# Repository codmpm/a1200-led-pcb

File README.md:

# A1200 LED PCB

This is a simple replacement for the original LED PCB of an Amiga 1200.

On refurbishment of my original PCB, some traces broke of as the thing is something around 30 years old ;-)
The only thing I've added, is the possibility to use 1206 33Ω resistor instead of the throughhole ones.

The Boards can be ordered at Aisler: [https://aisler.net/p/QBTDPKHQ](https://aisler.net/p/QBTDPKHQ)

If you want something more fancy or current, please check BiFrost oder other LED solutions from the different shops and people, who create them on the ever active amiga community, e.g. https://www.a1k.org/forum/.

## License
CC-BY-SA, 2019 Patrik Mayer

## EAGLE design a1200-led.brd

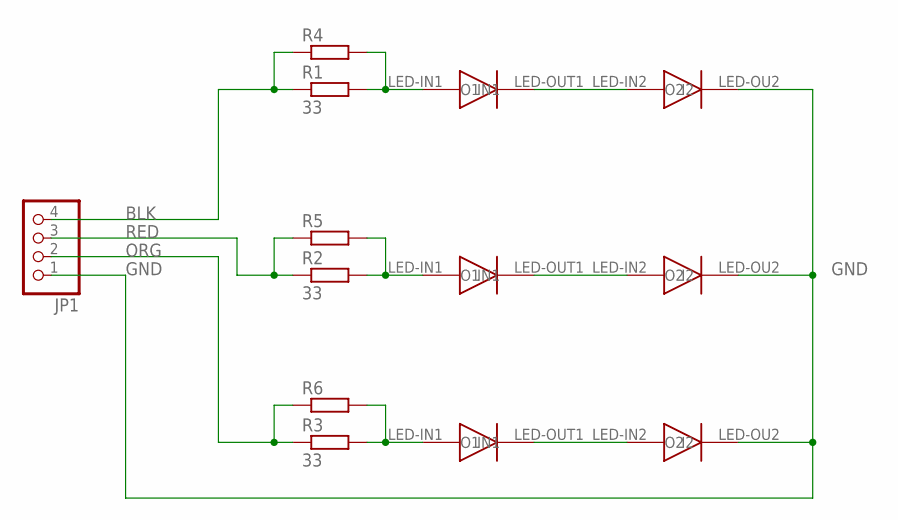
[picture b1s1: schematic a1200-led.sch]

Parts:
JP1: PINHD-1X4; 1X04
LED1, LED2, LED3: A1200-LED
R1, R2, R3: 33; 0207/10
R4, R5, R6: R-EU_R1206; R1206

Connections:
BLK: JP1.4, R1.1, R4.1
GND: JP1.1, LED1.LED-OU2 (O2), LED2.LED-OU2 (O2), LED3.LED-OU2 (O2)
unnamed: LED1.LED-IN1 (IN1), R1.2, R4.2
unnamed: LED1.LED-IN2 (I2), LED1.LED-OUT1 (O1)
unnamed: LED2.LED-IN1 (IN1), R2.2, R5.2
unnamed: LED2.LED-IN2 (I2), LED2.LED-OUT1 (O1)
unnamed: LED3.LED-IN1 (IN1), R3.2, R6.2
unnamed: LED3.LED-IN2 (I2), LED3.LED-OUT1 (O1)
ORG: JP1.2, R3.1, R6.1
RED: JP1.3, R2.1, R5.1

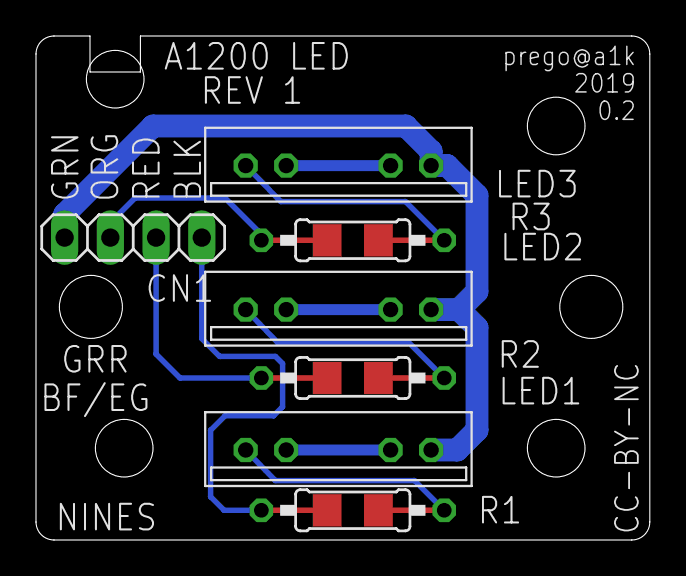
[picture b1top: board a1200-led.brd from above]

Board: 2 copper layers, 34.1 x 28.0 mm, 10 parts (0 on the bottom side), 10 nets.

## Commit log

2019-04-18 ordered v0.1
2019-04-18 fixed led pin width, v0.2
2019-04-18 added readme
2019-04-18 minor fixes on the holes
2019-04-18 refined readme
2024-04-20 Update README.md
    added aisler link
2024-09-27 added gerbers, works with jlcpcb

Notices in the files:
a1200-led.brd:
CC-BY-NC
